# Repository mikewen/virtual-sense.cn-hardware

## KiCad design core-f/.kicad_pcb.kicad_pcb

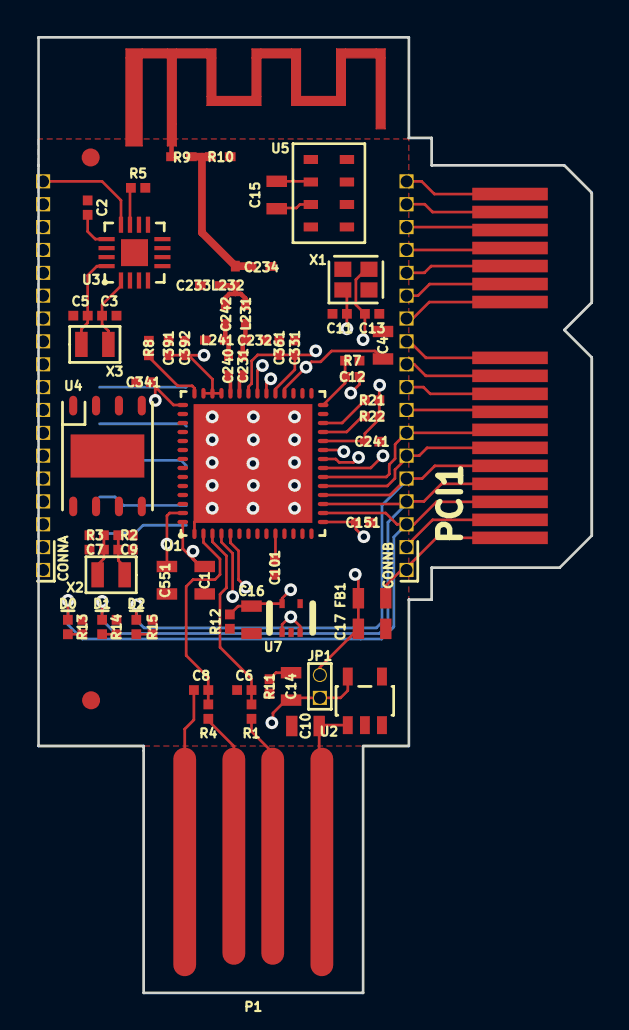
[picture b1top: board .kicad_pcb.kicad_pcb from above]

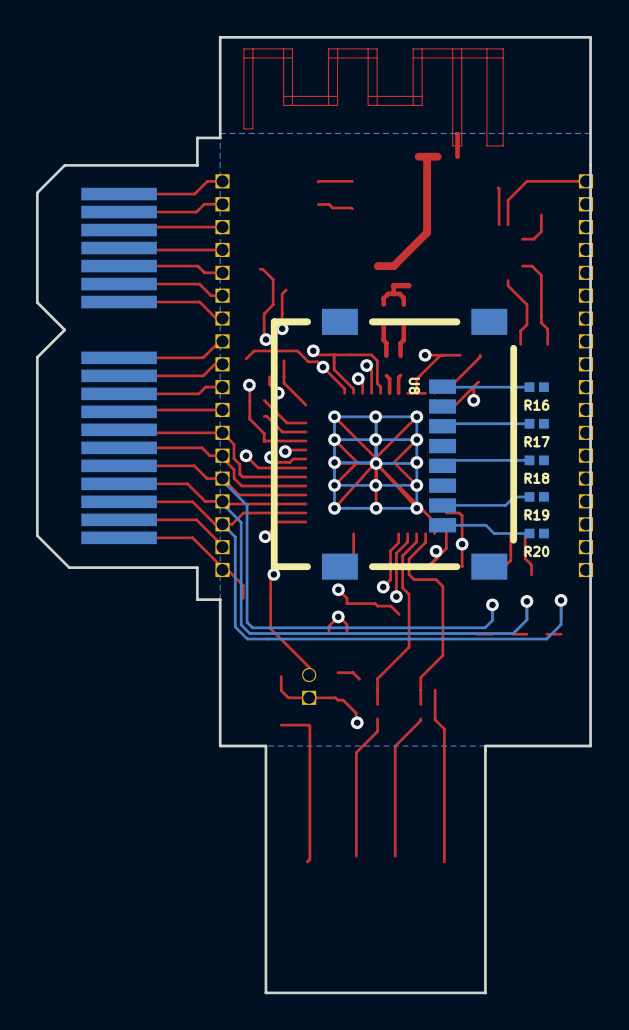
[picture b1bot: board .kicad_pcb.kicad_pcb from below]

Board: 4 copper layers, 30.7 x 53.1 mm, 78 parts (6 on the bottom side), 69 nets.

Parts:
C1, C4, C10, C14, C15, C551: 1uF; VSCN_SM0603
C2: 100n; VSCN_SM0402
C3, C5: 18p; VSCN_SM0402
C6, C8: 47pF; VSCN_SM0402
C7, C9, C11, C13: 22pF; VSCN_SM0402
C12: 1nF; VSCN_SM0402
C16: 47uF; VSCN_SM0603
C17: 2.2uF; VSCN_SM0603
C101, C151, C241, C331, C341, C361, C391: 100nF; VSCN_SM0402
C231, C240: 100pF; VSCN_SM0402_F-ANTENNA
C232, C242: 1pF; VSCN_SM0402_F-ANTENNA
C233: 1.8pF; VSCN_SM0402_F-ANTENNA
C234: 1.5pF; VSCN_SM0402_F-ANTENNA
C392: 220pF; VSCN_SM0402
CONNA1: CONNA; VSCN_SIL-18_1P27S
CONNB1: CONNB; VSCN_SIL-18_1P27S
D0, D1, D2: LED; VSCN_SM0402_POL
FB1: BLM18HE152SN1; VSCN_SM0603
JP1: JUMPER; VSCN_PIN_ARRAY_2X1
L231, L232, L241: 1.2nH; VSCN_SM0402_F-ANTENNA
P1: USB-PLUG; VSCN_USB-A_PCB-PLUG
P5, P6: CONN_1; fiducial15
PCI1: CONN_18X2; CONN_PCI_2X18_IN
R1, R4: 33; VSCN_SM0402
R2, R3: 0; VSCN_SM0402
R5: 47K; VSCN_SM0402
R7: 2.2K; VSCN_SM0402
R8: 56K; VSCN_SM0402
R9: 0; VSCN_SM0402_F-ANTENNA
R10: NO; VSCN_SM0402_F-ANTENNA
R11, R13, R14, R15: RSML; VSCN_SM0402
R12: 4.4K; VSCN_SM0402
R16, R17, R18, R19, R20, R21, R22: 10K; VSCN_SM0402
U1: CC2538; QFN-N56
U2: TPS76933; VSCN-SOT23-5
U3: PCF2123BS; QFN-N16
U4: VSCN-24AA512; VSCN-DFN_6X5
U5: MPL115A2
U6: VSCN_2_4_F-ANTENNA
U7: BH1620FVC1; BH1620FVC
U8: MICRO_SD
X1: 32MHz; FA-128_32MH
X2, X3: 32.768kHz; FC-12M_32_768KH

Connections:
ADC/DIO/GPIO/PA3: CONNB1.6, PCI1.B6, U1.19
ADC/DIO/GPIO/PA6: CONNB1.9, PCI1.B9, U1.22
ADC_LIGHT/PA7: C16.1, R12.1, U1.23, U7.5
BAR_EN/PB1: U1.54, U5.1, U5.4, U5.5
CLKOUT: CONNA1.18, PCI1.A18, U3.12
CMPN/ADC/DIO/GPIO/PA4: CONNB1.7, PCI1.B7, U1.20
CMPP/ADC/DIO/GPIO/PA5: CONNB1.8, PCI1.B8, U1.21
E2PROM_EN/PB2: U1.53, U4.1, U4.2, U4.3, U4.8
GND: C1.2, C2.2, C3.1, C4.2, C5.1, C6.2, C7.2, C8.2, C9.2, C10.2, C11.2, C12.1, C13.2, C15.2, C16.2, C17.1, C101.2, C151.2, C232.1, C233.1, C234.1, C241.2, C331.2, C341.2, C361.2, C391.2, C392.2, C551.2, CONNA1.2, CONNB1.2, L241.1, P1.4, PCI1.A2, PCI1.B2, R5.2, R8.2, R10.2, R11.2, R12.2, R13.2, R14.2, R15.2, U1.1, U1.57, U2.2, U2.3, U3.5, U3.17, U4.4, U4.7, U5.3, U6.2, U7.2, U7.4, U8.6, X1.2, X1.4
GPIO/PC4: CONNA1.6, PCI1.A6, U1.9
GPIO/PC5: CONNA1.7, PCI1.A7, U1.8
GPIO/PC6: CONNA1.8, PCI1.A8, U1.7
GPIO/PC7: CONNA1.9, PCI1.A9, U1.6
GPIO/PD5: CONNA1.15, PCI1.A15, U1.31
HP-GPIO/PC0: CONNB1.18, PCI1.B18, U1.14
HP-GPIO/PC1: CONNA1.3, PCI1.A3, U1.13
HP-GPIO/PC2: CONNA1.4, PCI1.A4, U1.12
HP-GPIO/PC3: CONNA1.5, PCI1.A5, U1.11
JTAG_TCK: CONNB1.13, PCI1.B13, U1.47
JTAG_TDI/PB6: CONNB1.15, PCI1.B15, U1.49
JTAG_TDO/PB7: CONNB1.16, PCI1.B16, U1.48
JTAG_TMS: CONNB1.14, PCI1.B14, U1.46
LED0/ROM_BL _RXD/PA0: CONNB1.3, D0.1, PCI1.B3, U1.16
LED1/ROM_BL _TXD/PA1: CONNB1.4, D1.1, PCI1.B4, U1.17
LED2/ROM_BL _SEL/PA2: CONNB1.5, D2.1, PCI1.B5, U1.18
LIGHT_EN/PB0: U1.5, U7.1, U7.3
MISO/GPIO/PD2: CONNA1.12, PCI1.A12, R19.2, U1.27, U3.8, U8.7
MOSI/GPIO/PD3: CONNA1.13, PCI1.A13, R17.2, U1.29, U3.9, U8.3
unnamed: P1.2, R1.1
unnamed: P1.3, R4.1
unnamed: C7.1, R3.2, X2.1
unnamed: C14.2, R11.1
unnamed: C1.1, C4.1, U1.32, U1.56
unnamed: C240.2, U1.38
unnamed: C231.1, U1.37
unnamed: C12.2, R7.1, U1.28
unnamed: C5.2, U3.16, X3.2
unnamed: R8.1, U1.42
unnamed: C234.2, L232.2, R9.1, R10.1
unnamed: R9.2, U6.1
unnamed: R20.2, U8.8
unnamed: R16.2, U8.1
unnamed: C233.2, C242.1, L231.2, L232.1
unnamed: C240.1, C242.2, L241.2
unnamed: C231.2, C232.2, L231.1
unnamed: C9.1, R2.2, X2.2
unnamed: D1.2, R14.1
unnamed: D0.2, R13.1
unnamed: D2.2, R15.1
unnamed: C15.1, U5.2
unnamed: R5.1, U3.11
unnamed: C3.2, U3.1, X3.1
RESET_N: CONNB1.12, PCI1.B12, R7.2
RTC_EN/PB3: U1.52, U3.4
RTC_INT/PB4: U1.51, U3.3
SCK/GPIO/PD4: CONNA1.14, PCI1.A14, R18.2, U1.30, U3.10, U8.5
SCL/GPIO/PD1: CONNA1.11, PCI1.A11, R21.2, U1.26, U4.6, U5.8
SDA/GPIO/PD0: CONNA1.10, PCI1.A10, R22.2, U1.25, U4.5, U5.7
SD_EN/GPIO/PB5: CONNB1.17, PCI1.B17, U1.50, U8.2
USB_N: C6.1, CONNB1.11, PCI1.B11, R1.2, U1.3
USB_P: C8.1, CONNB1.10, PCI1.B10, R4.2, U1.2
VBUS: C10.1, P1.1, U2.1
VDD: C2.1, C17.2, C101.1, C151.1, C241.1, C331.1, C341.1, C361.1, C391.1, C392.1, C551.1, FB1.1, JP1.2, R16.1, R17.1, R18.1, R19.1, R20.1, R21.1, R22.1, U1.10, U1.15, U1.24, U1.33, U1.36, U1.39, U1.40, U1.41, U1.43, U1.55, U3.13, U8.4
VDD_EB: CONNA1.1, CONNB1.1, FB1.2, PCI1.A1, PCI1.B1
VDD_USB: C14.1, JP1.1, U1.4, U2.5
XOSC32K_Q1/PD6: CONNA1.16, PCI1.A16, R3.1, U1.44
XOSC32K_Q2/PD7: CONNA1.17, PCI1.A17, R2.1, U1.45
XPSC32M_Q1: C13.1, U1.34, X1.3
XPSC32M_Q2: C11.1, U1.35, X1.1

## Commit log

2015-02-26 Insert as head VSCN32 test hardware
